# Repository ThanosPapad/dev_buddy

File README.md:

# DevBuddy V1
## An engineer's assistant in development.
*DevBuddy is a project under development aimed to provide engineers with an easy platform to prototype embeeded systems.*

It provides vast options in voltages to be used to supply the target board, current consumption meassurements for all channels, serial communication options and lastly a PC app to monitor and control it.
Should be able to be used for the starting point of any custom testing rig

### File breakdown
* __DevBuddy_mk1__ - _Hardware files in KiCad_.
* __Scripts__ - _Python script for the PC app_.
* __dev_buddy_v1__ - _Firmware for the RP2350 MCU / Device_.
* __Resources__ - _You can find the current PCB schematic PDF and screenshots_.

### Current capabilities
* All communication is happening over UART
* Control digital outputs commanded by the APP
* Reading digital inputs commanded by the APP
* The device is capable of reporting back to the APP measurements of Voltages and Currents of 8 channels, with the ability to switch on or off the function as well as the intervals of the reporting
* The APP looks cool as hell!
* Added support for two 8-Bit DACs for APP and Device
* Added two controllable voltage channels on PCB, firmware will have to come later
* A first version of the dispatcher is operational
* There are three channels of UART communication available to the device and APP

There are more screenshots in the folder showcasing the app

### Things that need to be done
* Software (I2C)for the variable voltage channels control
* The ability to record sessions of measuremnts, propably saved as CSV files
* The ability to choose analog channels and view the measurements in a graph would be quite cool as well
* The schematic should progressing quicker
* Need to figure out how the external channels will work, and If external I2C is needed as well
* Add ability for actions from external interrupts, that means one or two pins accessible to the user

More updates to come soon!

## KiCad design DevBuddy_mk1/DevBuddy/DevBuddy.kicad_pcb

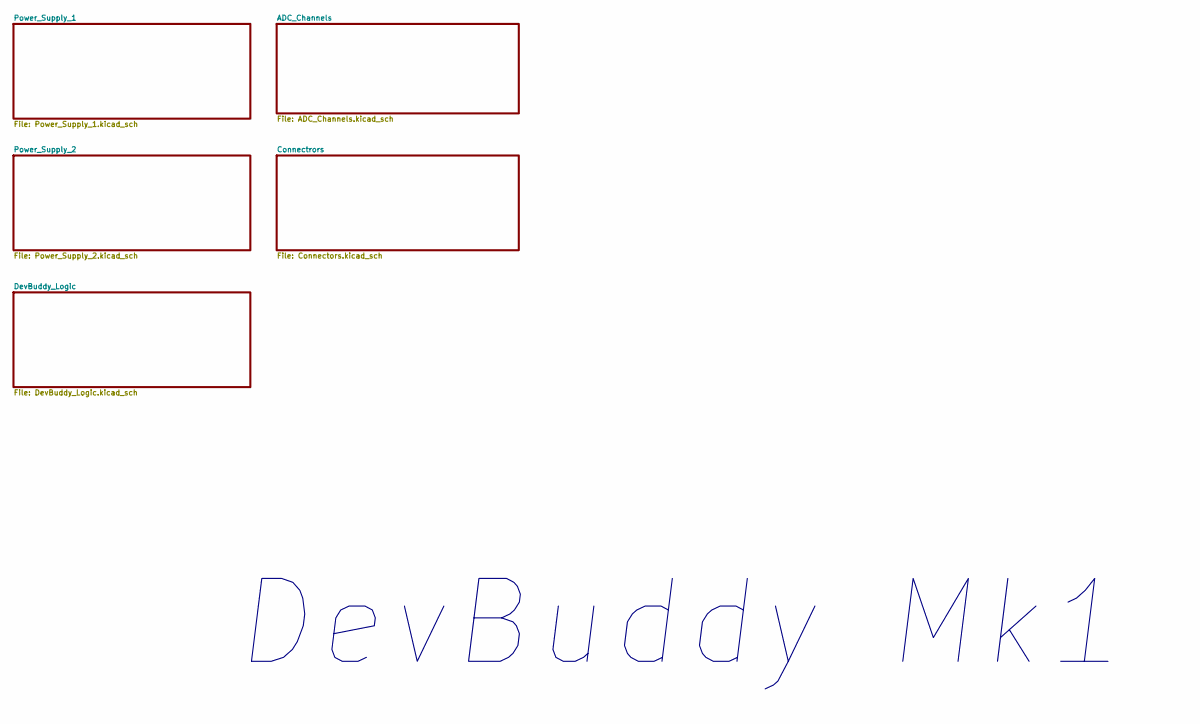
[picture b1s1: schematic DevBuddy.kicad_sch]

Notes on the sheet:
DevBuddy Mk1

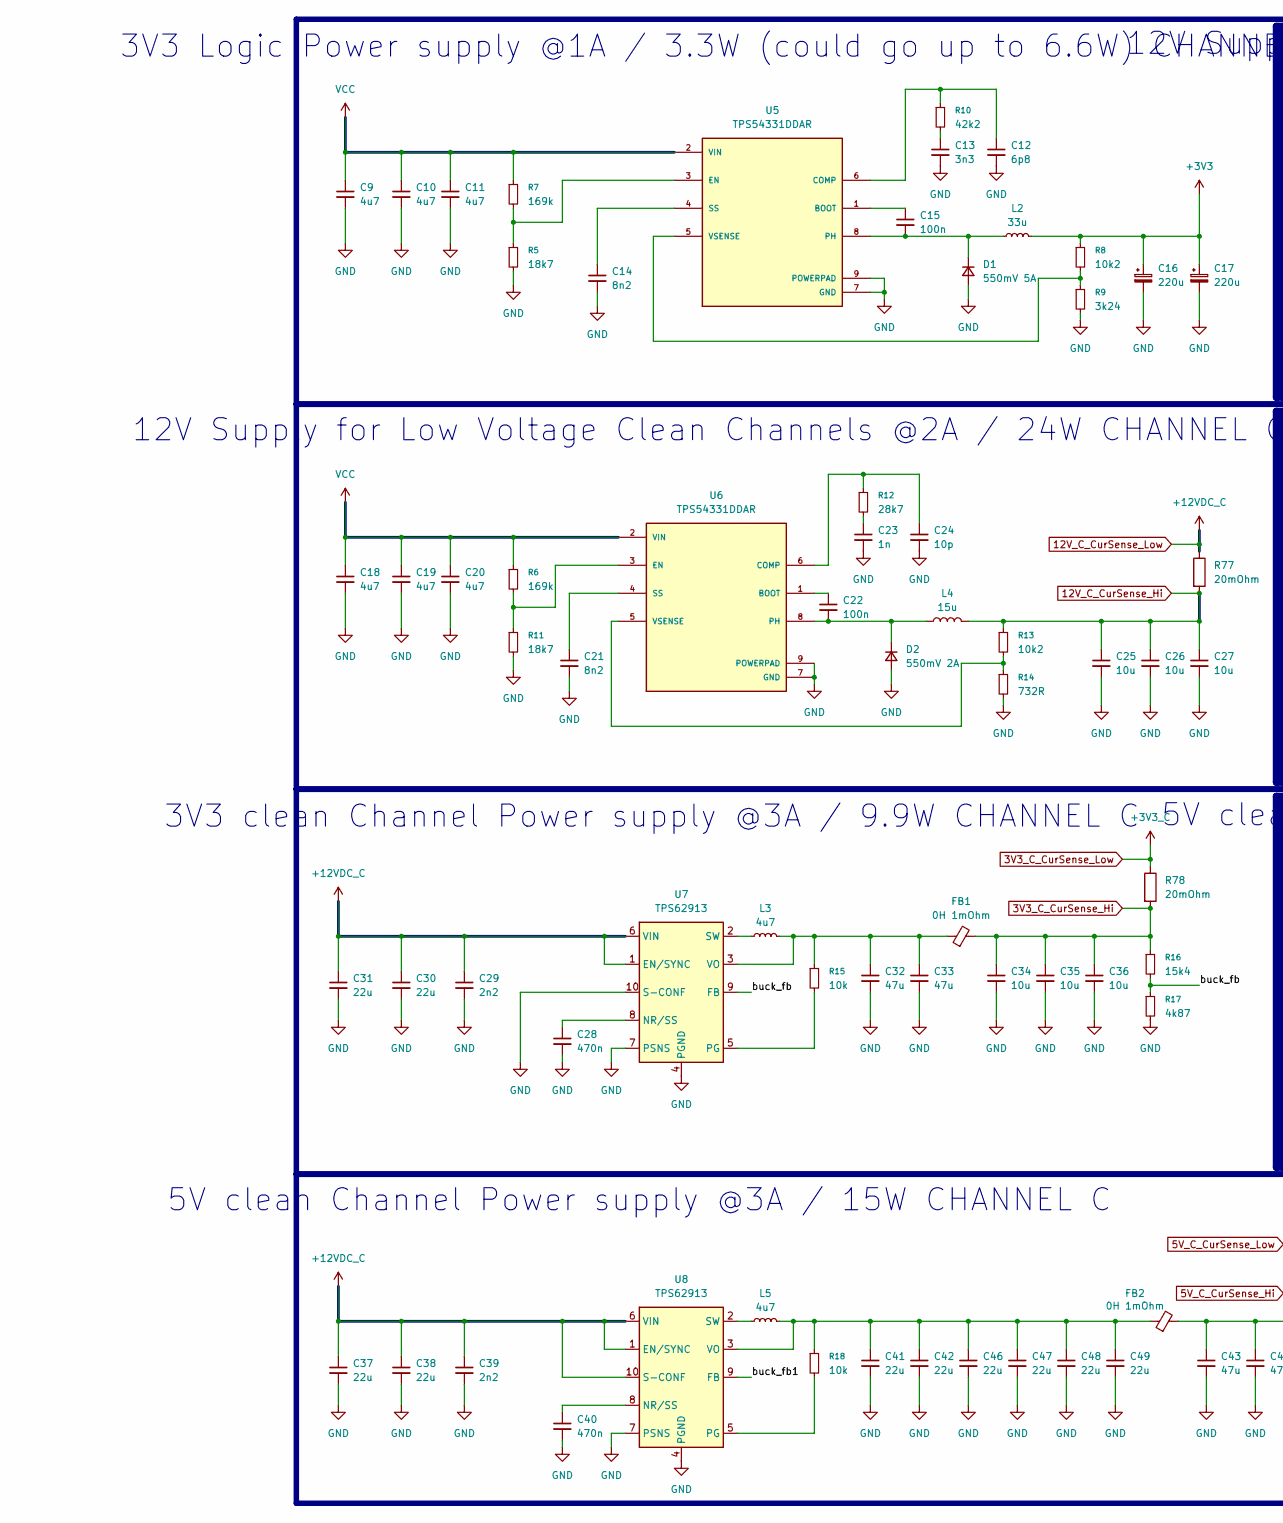
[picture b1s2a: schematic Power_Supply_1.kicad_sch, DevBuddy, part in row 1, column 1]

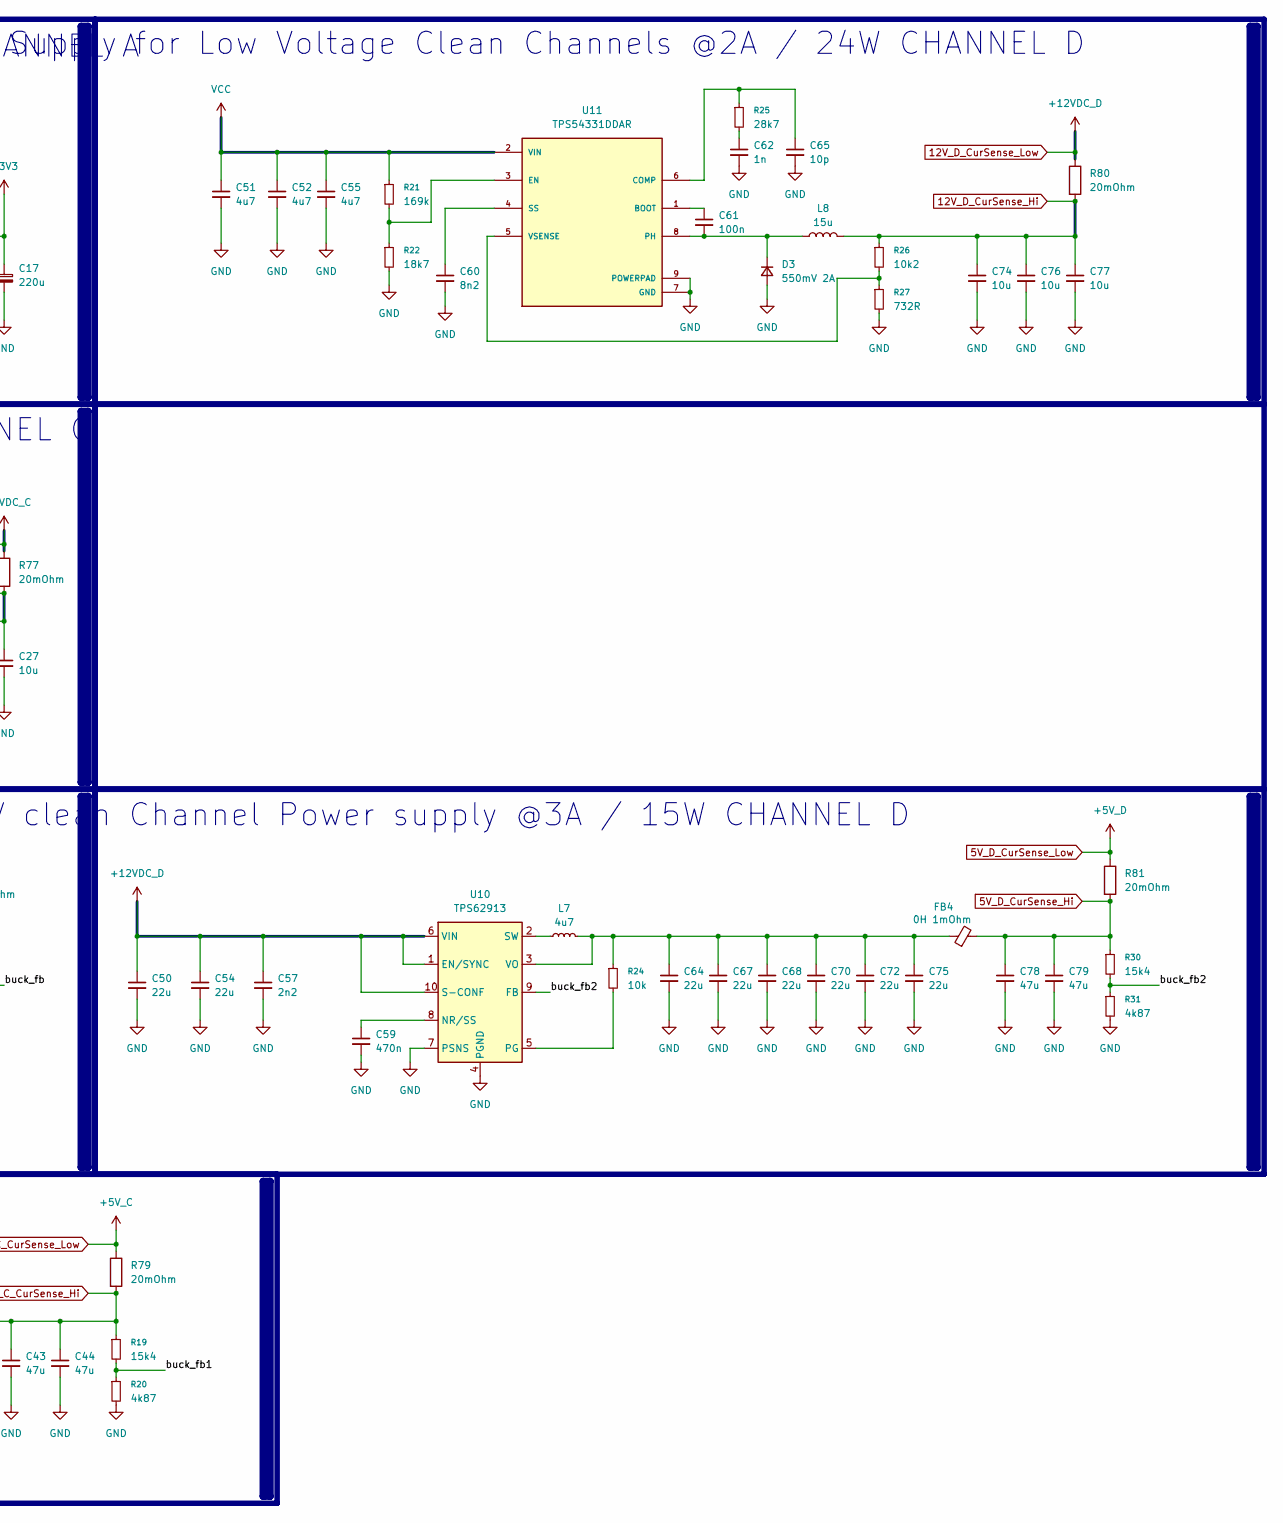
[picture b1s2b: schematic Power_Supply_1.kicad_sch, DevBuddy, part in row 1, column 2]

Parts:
C9, C10, C11, C18, C19, C20, C51, C52, C55: 4u7; C_1210_3225Metric
C12: 6p8; C_0402_1005Metric
C13: 3n3; C_0402_1005Metric
C14, C21, C60: 8n2; C_0402_1005Metric
C15, C22, C61: 100n; C_0805_2012Metric
C16, C17: 220u; CP_Elec_6.3x5.4
C23, C62: 1n; C_0402_1005Metric
C24, C65: 10p; C_0402_1005Metric
C25, C26, C27, C74, C76, C77: 10u; C_1210_3225Metric
C28, C40, C59: 470n; C_0402_1005Metric
C29, C39, C57: 2n2; C_0402_1005Metric
C30, C31, C37, C38, C41, C42, C46, C47, C48, C49, C50, C54, C64, C67, C68, C70, C72, C75: 22u; C_0805_2012Metric
C32, C33, C43, C44, C78, C79: 47u; C_0805_2012Metric
C34, C35, C36: 10u; C_0805_2012Metric
D1: 550mV 5A; D_SMC
D2, D3: 550mV 2A; D_SMC
FB1, FB2, FB4: 0H 1mOhm; Fuse_1206_3216Metric
L2: 33u; L_Coilcraft_MSS1210-XXX
L3, L5, L7: 4u7; L_Coilcraft_XAL6060-XXX
L4, L8: 15u; L_Bourns_SRR1260
R5, R11, R22: 18k7; R_0402_1005Metric
R6, R7, R21: 169k; R_0402_1005Metric
R8, R13, R26: 10k2; R_0402_1005Metric
R9: 3k24; R_0402_1005Metric
R10: 42k2; R_0402_1005Metric
R12, R25: 28k7; R_0402_1005Metric
R14, R27: 732R; R_0402_1005Metric
R15, R18, R24: 10k; R_0402_1005Metric
R16, R19, R30: 15k4; R_0402_1005Metric
R17, R20, R31: 4k87; R_0402_1005Metric
R77, R78, R79, R80, R81: 20mOhm; R_1210_3225Metric
U5, U6, U11: TPS54331DDAR; CONV_TPS54331DDAR; PARTREV F
U7, U8, U10: TPS62913; Texas_RPU0010A_VQFN-HR-10_2x2mm_P0.5mm

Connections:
3V3_C_CurSense_Hi: C34.1, C35.1, C36.1, FB1.2, R16.1, R78.2; also elsewhere on the board
3V3_C_CurSense_Low: R78.1; also elsewhere on the board
5V_C_CurSense_Hi: C43.1, C44.1, FB2.2, R19.1, R79.2; also elsewhere on the board
5V_C_CurSense_Low: R79.1; also elsewhere on the board
5V_D_CurSense_Hi: C78.1, C79.1, FB4.2, R30.1, R81.2; also elsewhere on the board
5V_D_CurSense_Low: R81.1; also elsewhere on the board
12V_C_CurSense_Hi: C25.1, C26.1, C27.1, L4.2, R13.1, R77.2; also elsewhere on the board
12V_C_CurSense_Low: C29.1, C30.1, C31.1, C37.1, C38.1, C39.1, R77.1, U7.1 (EN/SYNC), U7.6 (VIN), U8.1 (EN/SYNC), U8.6 (VIN), U8.10 (S-CONF); also elsewhere on the board
12V_D_CurSense_Hi: C74.1, C76.1, C77.1, L8.2, R26.1, R80.2; also elsewhere on the board
12V_D_CurSense_Low: C50.1, C54.1, C57.1, R80.1, U10.1 (EN/SYNC), U10.6 (VIN), U10.10 (S-CONF); also elsewhere on the board
+3V3: C16.1, C17.1, L2.2, R8.1; also elsewhere on the board
/Power_Supply_1/buck_fb: R16.2, R17.1, U7.9 (FB)
/Power_Supply_1/buck_fb1: R19.2, R20.1, U8.9 (FB)
/Power_Supply_1/buck_fb2: R30.2, R31.1, U10.9 (FB)
GND: C9.2, C10.2, C11.2, C12.2, C13.2, C14.2, C16.2, C17.2, C18.2, C19.2, C20.2, C21.2, C23.2, C24.2, C25.2, C26.2, C27.2, C28.2, C29.2, C30.2, C31.2, C32.2, C33.2, C34.2, C35.2, C36.2, C37.2, C38.2, C39.2, C40.2, C41.2, C42.2, C43.2, C44.2, C46.2, C47.2, C48.2, C49.2, C50.2, C51.2, C52.2, C54.2, C55.2, C57.2, C59.2, C60.2, C62.2, C64.2, C65.2, C67.2, C68.2, C70.2, C72.2, C74.2, C75.2, C76.2, C77.2, C78.2, C79.2, D1.2 (A), D2.2 (A), D3.2 (A), R5.2, R9.2, R11.2, R14.2, R17.2, R20.2, R22.2, R27.2, R31.2, U5.7 (GND), U5.9 (POWERPAD), U6.7 (GND), U6.9 (POWERPAD), U7.4 (PGND), U7.7 (PSNS), U7.10 (S-CONF), U8.4 (PGND), U8.7 (PSNS), U10.4 (PGND), U10.7 (PSNS), U11.7 (GND), U11.9 (POWERPAD); also elsewhere on the board
unnamed: C13.1, R10.2
unnamed: C23.1, R12.2
unnamed: C62.1, R25.2
unnamed: C15.2, D1.1 (K), L2.1, U5.8 (PH)
unnamed: C22.2, D2.1 (K), L4.1, U6.8 (PH)
unnamed: C61.2, D3.1 (K), L8.1, U11.8 (PH)
unnamed: C15.1, U5.1 (BOOT)
unnamed: C12.1, R10.1, U5.6 (COMP)
unnamed: R5.1, R7.2, U5.3 (EN)
unnamed: C14.1, U5.4 (SS)
unnamed: R8.2, R9.1, U5.5 (VSENSE)
unnamed: C22.1, U6.1 (BOOT)
unnamed: C24.1, R12.1, U6.6 (COMP)
unnamed: R6.2, R11.1, U6.3 (EN)
unnamed: C21.1, U6.4 (SS)
unnamed: R13.2, R14.1, U6.5 (VSENSE)
unnamed: C28.1, U7.8 (NR/SS)
unnamed: R15.2, U7.5 (PG)
unnamed: L3.1, U7.2 (SW)
unnamed: C32.1, C33.1, FB1.1, L3.2, R15.1, U7.3 (VO)
unnamed: C40.1, U8.8 (NR/SS)
unnamed: R18.2, U8.5 (PG)
unnamed: L5.1, U8.2 (SW)
unnamed: C41.1, C42.1, C46.1, C47.1, C48.1, C49.1, FB2.1, L5.2, R18.1, U8.3 (VO)
unnamed: C59.1, U10.8 (NR/SS)
unnamed: R24.2, U10.5 (PG)
unnamed: L7.1, U10.2 (SW)
unnamed: C64.1, C67.1, C68.1, C70.1, C72.1, C75.1, FB4.1, L7.2, R24.1, U10.3 (VO)
unnamed: C61.1, U11.1 (BOOT)
unnamed: C65.1, R25.1, U11.6 (COMP)
unnamed: R21.2, R22.1, U11.3 (EN)
unnamed: C60.1, U11.4 (SS)
unnamed: R26.2, R27.1, U11.5 (VSENSE)
VCC_CurSense_Low: C9.1, C10.1, C11.1, C18.1, C19.1, C20.1, C51.1, C52.1, C55.1, R6.1, R7.1, R21.1, U5.2 (VIN), U6.2 (VIN), U11.2 (VIN); also elsewhere on the board

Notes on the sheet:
12V Supply for Low Voltage Clean Channels @2A / 24W CHANNEL C
5V clean Channel Power supply @3A / 15W CHANNEL C
5V clean Channel Power supply @3A / 15W CHANNEL D
3V3 clean Channel Power supply @3A / 9.9W CHANNEL C
3V3 Logic Power supply @1A / 3.3W (could go up to 6.6W) CHANNEL A
12V Supply for Low Voltage Clean Channels @2A / 24W CHANNEL D

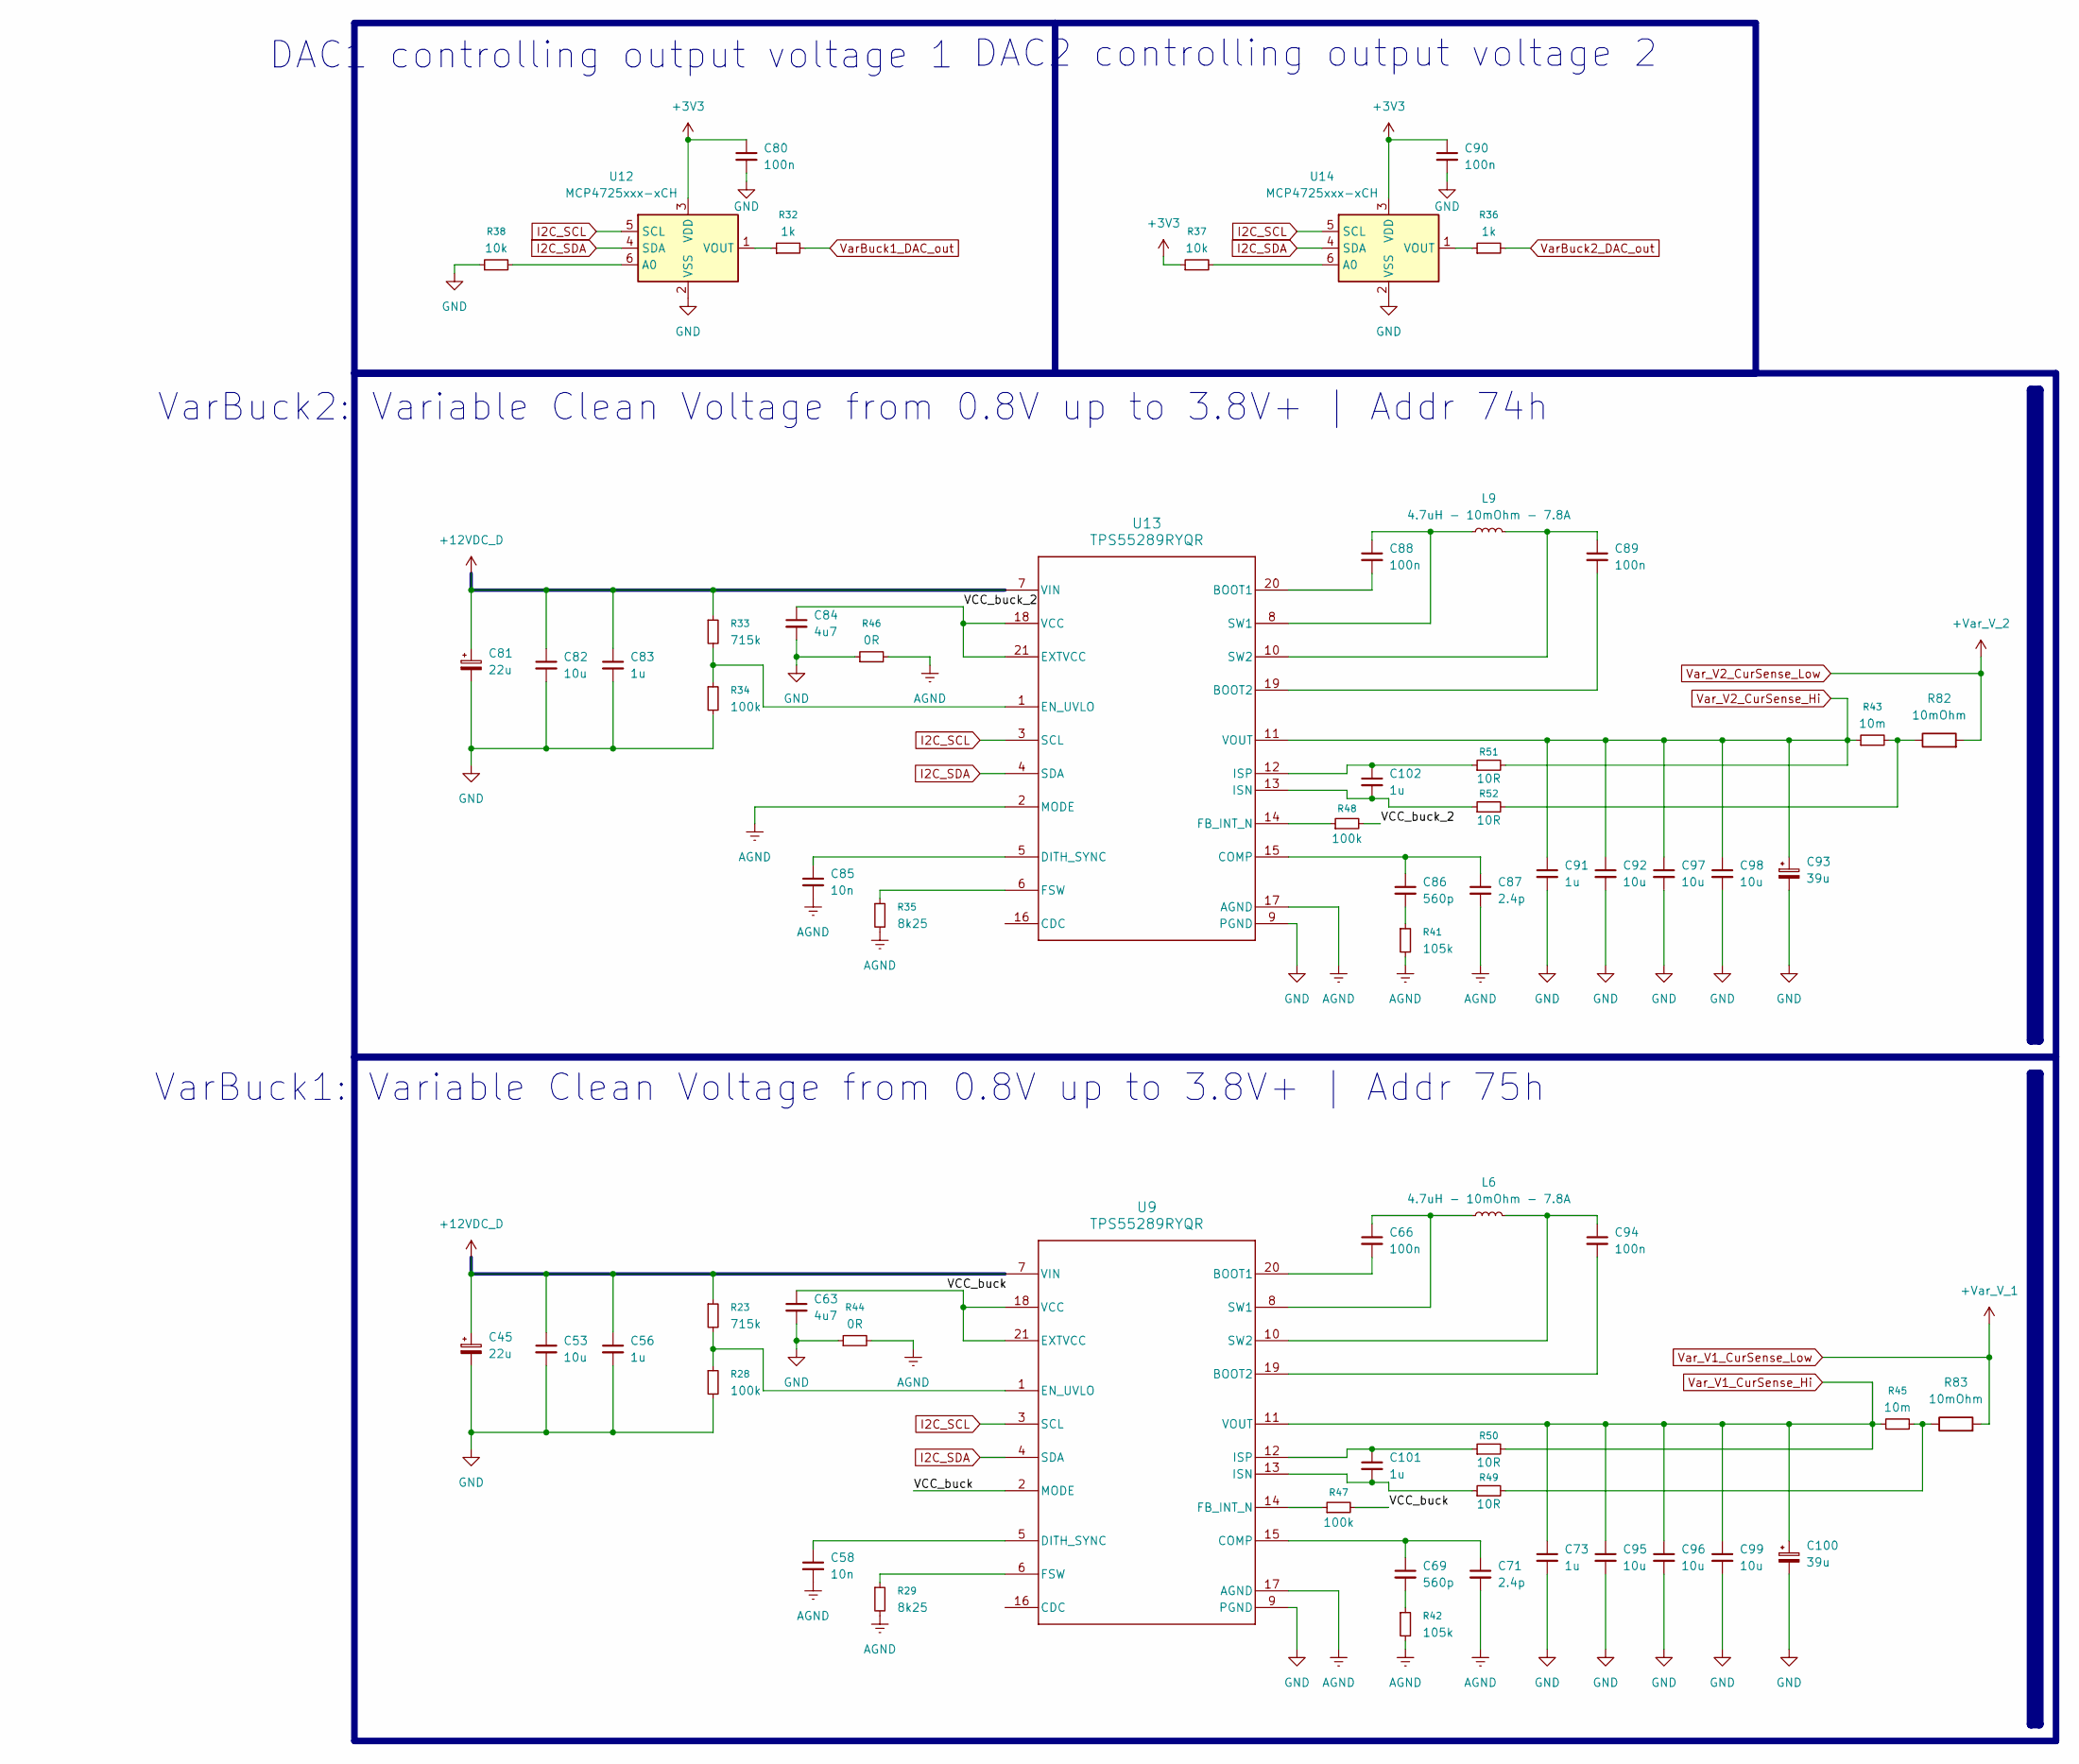
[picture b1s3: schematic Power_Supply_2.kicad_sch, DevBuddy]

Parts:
C45, C81: 22u; CP_EIA-7343-31_Kemet-D
C53, C82: 10u; C_1210_3225Metric
C56, C83, C101, C102: 1u; C_0402_1005Metric
C58, C85: 10n; C_0402_1005Metric
C63, C84: 4u7; C_0603_1608Metric
C66, C88, C89, C94: 100n; C_0603_1608Metric
C69, C86: 560p; C_0402_1005Metric
C71, C87: 2.4p; C_0402_1005Metric
C73, C91: 1u; C_0603_1608Metric
C80, C90: 100n; C_0402_1005Metric
C92, C95, C96, C97, C98, C99: 10u; C_0805_2012Metric
C93, C100: 39u; CP_Elec_5x5.9
L6, L9: 4.7uH - 10mOhm - 7.8A; L_Bourns-SRN8040_8x8.15mm
R23, R33: 715k; R_0402_1005Metric
R28, R34, R47, R48: 100k; R_0402_1005Metric
R29, R35: 8k25; R_0402_1005Metric
R32, R36: 1k; R_0402_1005Metric
R37, R38: 10k; R_0402_1005Metric
R41, R42: 105k; R_0402_1005Metric
R43, R45: 10m; R_1206_3216Metric
R44, R46: 0R; R_0402_1005Metric
R49, R50, R51, R52: 10R; R_0402_1005Metric
R82, R83: 10mOhm; R_1210_3225Metric
U9, U13: TPS55289RYQR; RYQ0021A-MFG
U12, U14: MCP4725xxx-xCH; SOT-23-6

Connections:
12V_D_CurSense_Low: C45.1, C53.1, C56.1, C81.1, C82.1, C83.1, R23.1, R33.1, U9.7 (VIN), U13.7 (VIN); also elsewhere on the board
+3V3: C80.1, C90.1, R37.1, U12.3 (VDD), U14.3 (VDD); also elsewhere on the board
/Power_Supply_2/VCC_buck: C63.1, R47.2, U9.2 (MODE), U9.18 (VCC), U9.21 (EXTVCC)
/Power_Supply_2/VCC_buck_2: C84.1, R48.2, U13.18 (VCC), U13.21 (EXTVCC)
AGND: C58.2, C71.2, C85.2, C87.2, R29.2, R35.2, R41.2, R42.2, R44.2, R46.2, U9.17 (AGND), U13.2 (MODE), U13.17 (AGND)
GND: C45.2, C53.2, C56.2, C63.2, C73.2, C80.2, C81.2, C82.2, C83.2, C84.2, C90.2, C91.2, C92.2, C93.2, C95.2, C96.2, C97.2, C98.2, C99.2, C100.2, R28.2, R34.2, R38.1, R44.1, R46.1, U9.9 (PGND), U12.2 (VSS), U13.9 (PGND), U14.2 (VSS); also elsewhere on the board
I2C_SCL: U9.3 (SCL), U12.5 (SCL), U13.3 (SCL), U14.5 (SCL); also elsewhere on the board
I2C_SDA: U9.4 (SDA), U12.4 (SDA), U13.4 (SDA), U14.4 (SDA); also elsewhere on the board
unnamed: C69.2, R42.1
unnamed: C86.2, R41.1
unnamed: R43.2, R52.2, R82.1
unnamed: R45.2, R49.2, R83.1
unnamed: C66.2, U9.20 (BOOT1)
unnamed: C94.2, U9.19 (BOOT2)
unnamed: C69.1, C71.1, U9.15 (COMP)
unnamed: C58.1, U9.5 (DITH_SYNC)
unnamed: R23.2, R28.1, U9.1 (EN_UVLO)
unnamed: R47.1, U9.14 (FB_INT_N)
unnamed: R29.1, U9.6 (FSW)
unnamed: C101.2, R49.1, U9.13 (ISN)
unnamed: C101.1, R50.1, U9.12 (ISP)
unnamed: C66.1, L6.1, U9.8 (SW1)
unnamed: C94.1, L6.2, U9.10 (SW2)
unnamed: R38.2, U12.6 (A0)
unnamed: R32.1, U12.1 (VOUT)
unnamed: C88.2, U13.20 (BOOT1)
unnamed: C89.2, U13.19 (BOOT2)
unnamed: C86.1, C87.1, U13.15 (COMP)
unnamed: C85.1, U13.5 (DITH_SYNC)
unnamed: R33.2, R34.1, U13.1 (EN_UVLO)
unnamed: R48.1, U13.14 (FB_INT_N)
unnamed: R35.1, U13.6 (FSW)
unnamed: C102.2, R52.1, U13.13 (ISN)
unnamed: C102.1, R51.1, U13.12 (ISP)
unnamed: C88.1, L9.1, U13.8 (SW1)
unnamed: C89.1, L9.2, U13.10 (SW2)
unnamed: R37.2, U14.6 (A0)
unnamed: R36.1, U14.1 (VOUT)
VarBuck1_DAC_out: R32.2; also elsewhere on the board
VarBuck2_DAC_out: R36.2; also elsewhere on the board
Var_V1_CurSense_Hi: C73.1, C95.1, C96.1, C99.1, C100.1, R45.1, R50.2, U9.11 (VOUT); also elsewhere on the board
Var_V1_CurSense_Low: R83.2; also elsewhere on the board
Var_V2_CurSense_Hi: C91.1, C92.1, C93.1, C97.1, C98.1, R43.1, R51.2, U13.11 (VOUT); also elsewhere on the board
Var_V2_CurSense_Low: R82.2; also elsewhere on the board

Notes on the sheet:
DAC1 controlling output voltage 1
VarBuck2: Variable Clean Voltage from 0.8V up to 3.8V+ | Addr 74h
VarBuck1: Variable Clean Voltage from 0.8V up to 3.8V+ | Addr 75h
DAC2 controlling output voltage 2

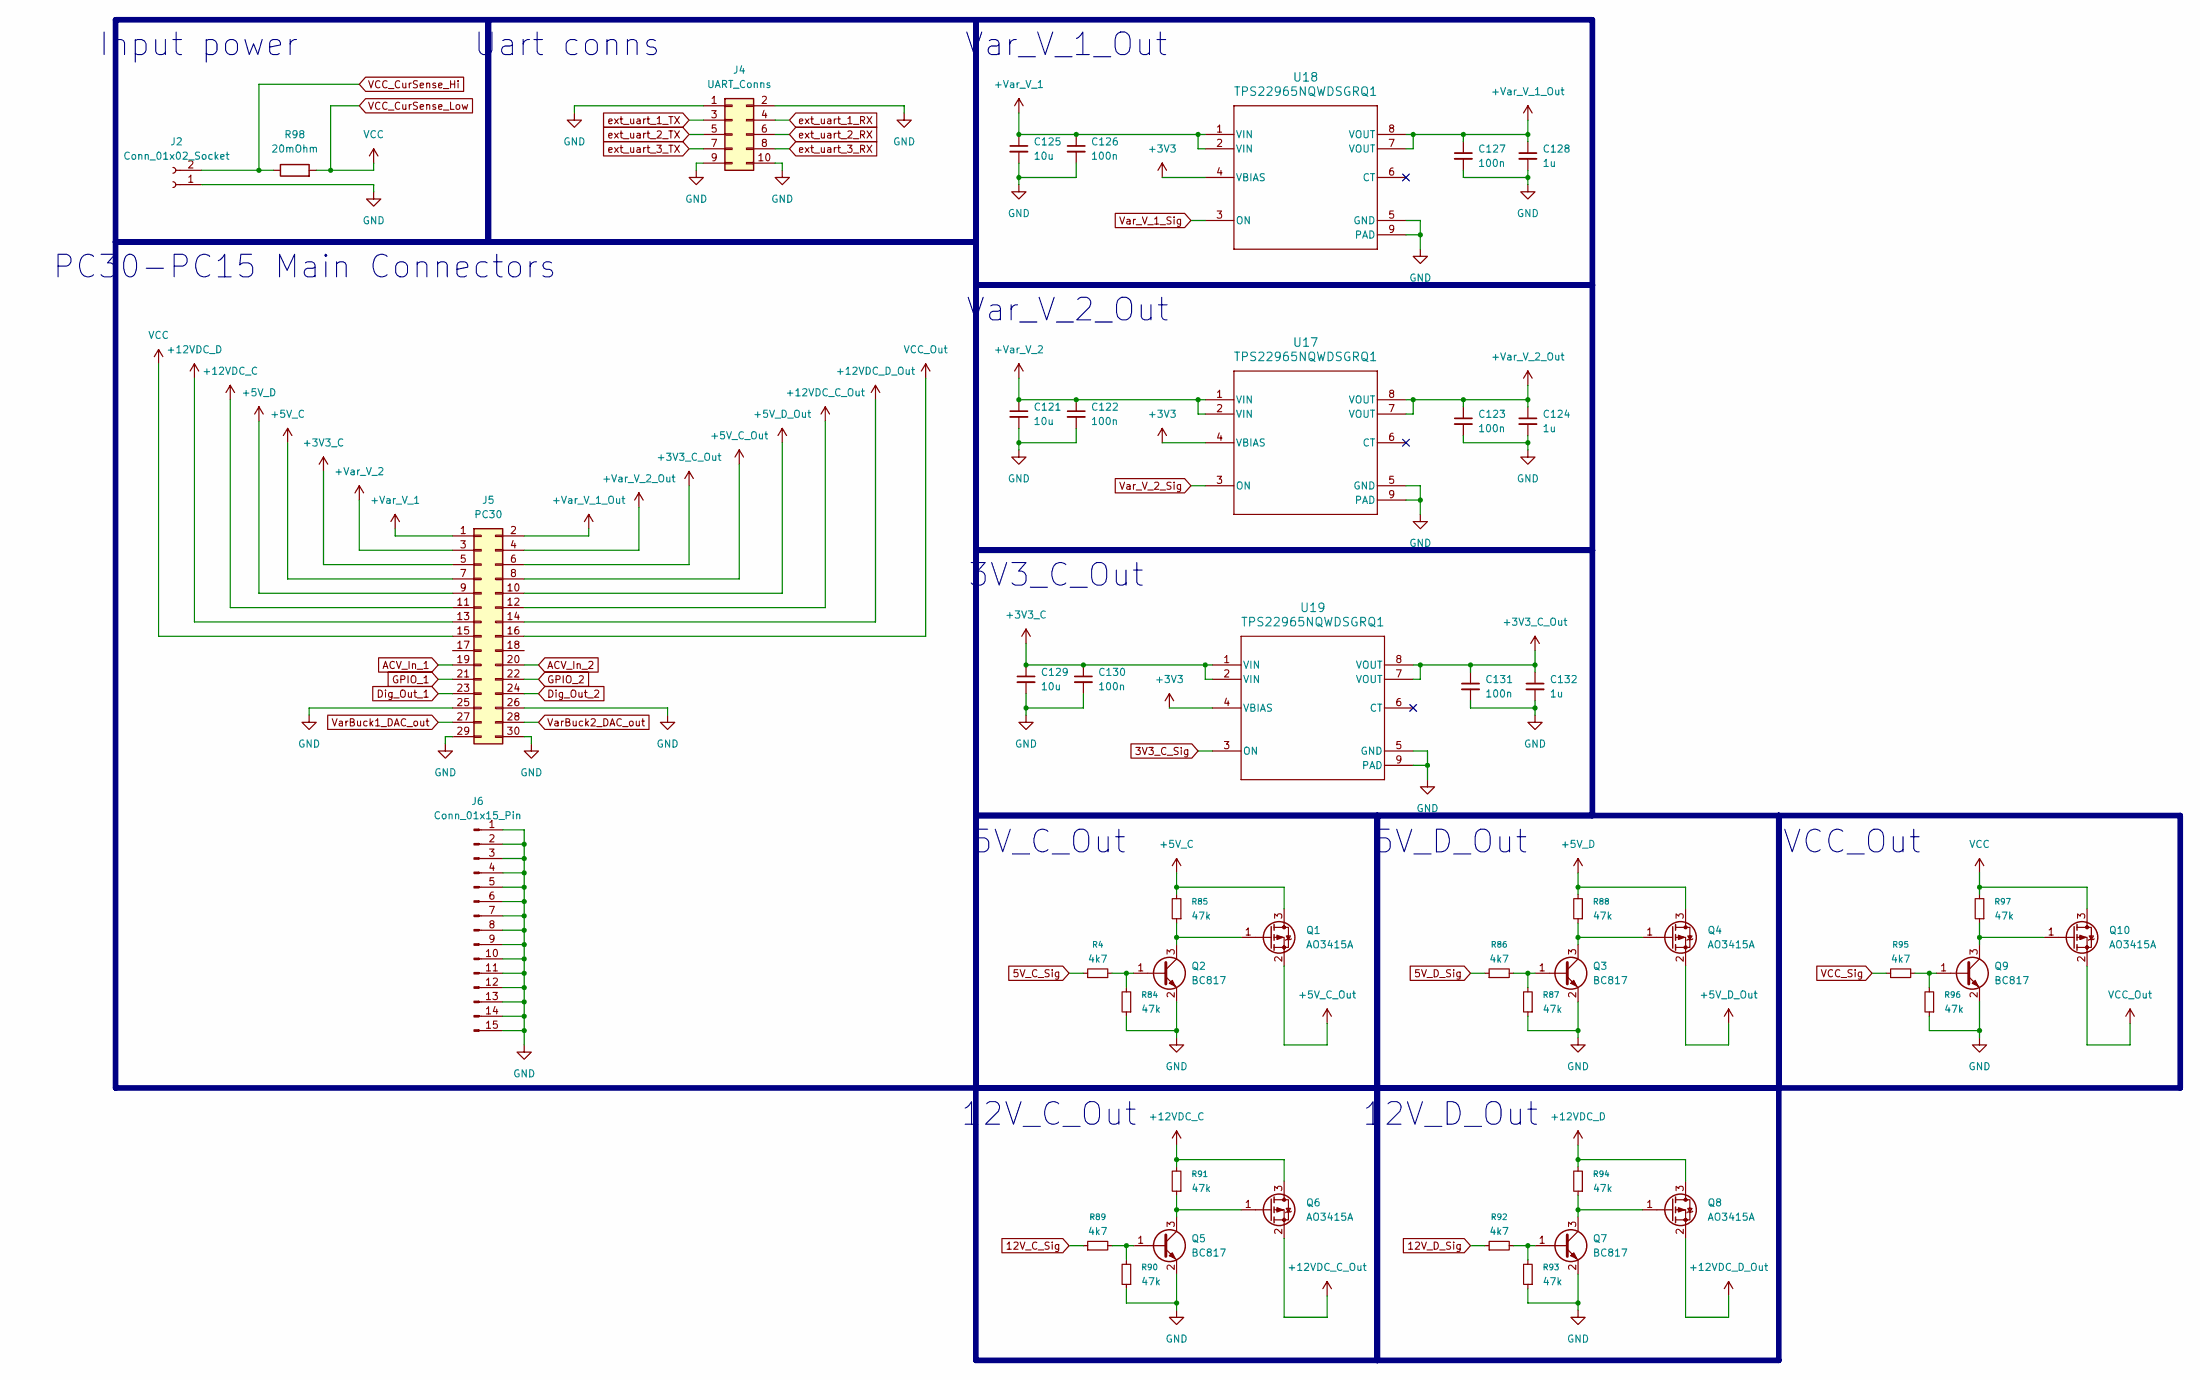
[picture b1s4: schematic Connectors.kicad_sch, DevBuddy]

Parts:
C121, C125, C129: 10u; C_1210_3225Metric
C122, C123, C126, C127, C130, C131: 100n; C_0402_1005Metric
C124, C128, C132: 1u; C_0402_1005Metric
J2: Conn_01x02_Socket; PhoenixContact_MC_1,5_2-G-5.08_1x02_P5.08mm_Horizontal
J4: UART_Conns; PinHeader_2x05_P2.54mm_Vertical_SMD
J5: PC30; PinHeader_2x15_P2.54mm_Vertical_SMD
J6: Conn_01x15_Pin; PinHeader_1x15_P2.54mm_Vertical_SMD_Pin1Left
Q1, Q4, Q6, Q8, Q10: AO3415A; SOT-23
Q2, Q3, Q5, Q7, Q9: BC817; SOT-23
R4, R86, R89, R92, R95: 4k7; R_0402_1005Metric
R84, R85, R87, R88, R90, R91, R93, R94, R96, R97: 47k; R_0402_1005Metric
R98: 20mOhm; R_1210_3225Metric
U17, U18, U19: TPS22965NQWDSGRQ1; DSG0008A_NV

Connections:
3V3_C_CurSense_Low: C129.1, C130.1, J5.5, U19.1 (VIN), U19.2 (VIN); also elsewhere on the board
3V3_C_Sig: U19.3 (ON); also elsewhere on the board
5V_C_CurSense_Low: J5.7, Q1.3 (D), R85.2; also elsewhere on the board
5V_C_Sig: R4.1; also elsewhere on the board
5V_D_CurSense_Low: J5.9, Q4.3 (D), R88.2; also elsewhere on the board
5V_D_Sig: R86.1; also elsewhere on the board
12V_C_CurSense_Low: J5.11, Q6.3 (D), R91.2; also elsewhere on the board
12V_C_Sig: R89.1; also elsewhere on the board
12V_D_CurSense_Low: J5.13, Q8.3 (D), R94.2; also elsewhere on the board
12V_D_Sig: R92.1; also elsewhere on the board
+3V3: U17.4 (VBIAS), U18.4 (VBIAS), U19.4 (VBIAS); also elsewhere on the board
+3V3_C_Out: C131.1, C132.1, J5.6, U19.7 (VOUT), U19.8 (VOUT)
+5V_C_Out: J5.8, Q1.2 (S)
+5V_D_Out: J5.10, Q4.2 (S)
+12VDC_C_Out: J5.12, Q6.2 (S)
+12VDC_D_Out: J5.14, Q8.2 (S)
+Var_V_1_Out: C127.1, C128.1, J5.2, U18.7 (VOUT), U18.8 (VOUT)
+Var_V_2_Out: C123.1, C124.1, J5.4, U17.7 (VOUT), U17.8 (VOUT)
ACV_In_1: J5.19; also elsewhere on the board
ACV_In_2: J5.20; also elsewhere on the board
Dig_Out_1: J5.23; also elsewhere on the board
Dig_Out_2: J5.24; also elsewhere on the board
GND: C121.2, C122.2, C123.2, C124.2, C125.2, C126.2, C127.2, C128.2, C129.2, C130.2, C131.2, C132.2, J2.1, J4.1, J4.2, J4.9, J4.10, J5.25, J5.26, J5.29, J5.30, J6.1, J6.2, J6.3, J6.4, J6.5, J6.6, J6.7, J6.8, J6.9, J6.10, J6.11, J6.12, J6.13, J6.14, J6.15, Q2.2 (E), Q3.2 (E), Q5.2 (E), Q7.2 (E), Q9.2 (E), R84.1, R87.1, R90.1, R93.1, R96.1, U17.5 (GND), U17.9 (PAD), U18.5 (GND), U18.9 (PAD), U19.5 (GND), U19.9 (PAD); also elsewhere on the board
GPIO_1: J5.21; also elsewhere on the board
GPIO_2: J5.22; also elsewhere on the board
unnamed: Q1.1 (G), Q2.3 (C), R85.1
unnamed: Q2.1 (B), R4.2, R84.2
unnamed: Q3.1 (B), R86.2, R87.2
unnamed: Q3.3 (C), Q4.1 (G), R88.1
unnamed: Q5.1 (B), R89.2, R90.2
unnamed: Q5.3 (C), Q6.1 (G), R91.1
unnamed: Q7.1 (B), R92.2, R93.2
unnamed: Q7.3 (C), Q8.1 (G), R94.1
unnamed: Q9.1 (B), R95.2, R96.2
unnamed: Q9.3 (C), Q10.1 (G), R97.1
VCC_CurSense_Hi: J2.2, R98.1; also elsewhere on the board
VCC_CurSense_Low: J5.15, Q10.3 (D), R97.2, R98.2; also elsewhere on the board
VCC_Out: J5.16, Q10.2 (S)
VCC_Sig: R95.1; also elsewhere on the board
VarBuck1_DAC_out: J5.27; also elsewhere on the board
VarBuck2_DAC_out: J5.28; also elsewhere on the board
Var_V1_CurSense_Low: C125.1, C126.1, J5.1, U18.1 (VIN), U18.2 (VIN); also elsewhere on the board
Var_V2_CurSense_Low: C121.1, C122.1, J5.3, U17.1 (VIN), U17.2 (VIN); also elsewhere on the board
Var_V_1_Sig: U18.3 (ON); also elsewhere on the board
Var_V_2_Sig: U17.3 (ON); also elsewhere on the board
ext_uart_1_RX: J4.4; also elsewhere on the board
ext_uart_1_TX: J4.3; also elsewhere on the board
ext_uart_2_RX: J4.6; also elsewhere on the board
ext_uart_2_TX: J4.5; also elsewhere on the board
ext_uart_3_RX: J4.8; also elsewhere on the board
ext_uart_3_TX: J4.7; also elsewhere on the board

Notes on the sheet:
Input power
5V_D_Out
12V_D_Out
VCC_Out
Var_V_1_Out
3V3_C_Out
PC30-PC15 Main Connectors
Uart conns
12V_C_Out
5V_C_Out
Var_V_2_Out
